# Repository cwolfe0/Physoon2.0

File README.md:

# Physoon2.0
This is the Eagle schematic and board file for the Physoon 2.0 (HAB Geiger Counters).
It externally interfaces with 2 geiger counters and processes the data before sending it via APRS and saving it on an SD card.

The board uses a:
- GPS
- Magnetometer
- MCU
- 5V Regulator
- 3.3V Regulator
- 6 Surefire CR123A in parallel sets of 3 in series.
- APRS-capable Radio
- 2 Logic Gates (for allowing 5V input to the radio from the MCU)
- Pressure Sensor
- Thermistor
- ON-MOM Switch
- PDI Interface

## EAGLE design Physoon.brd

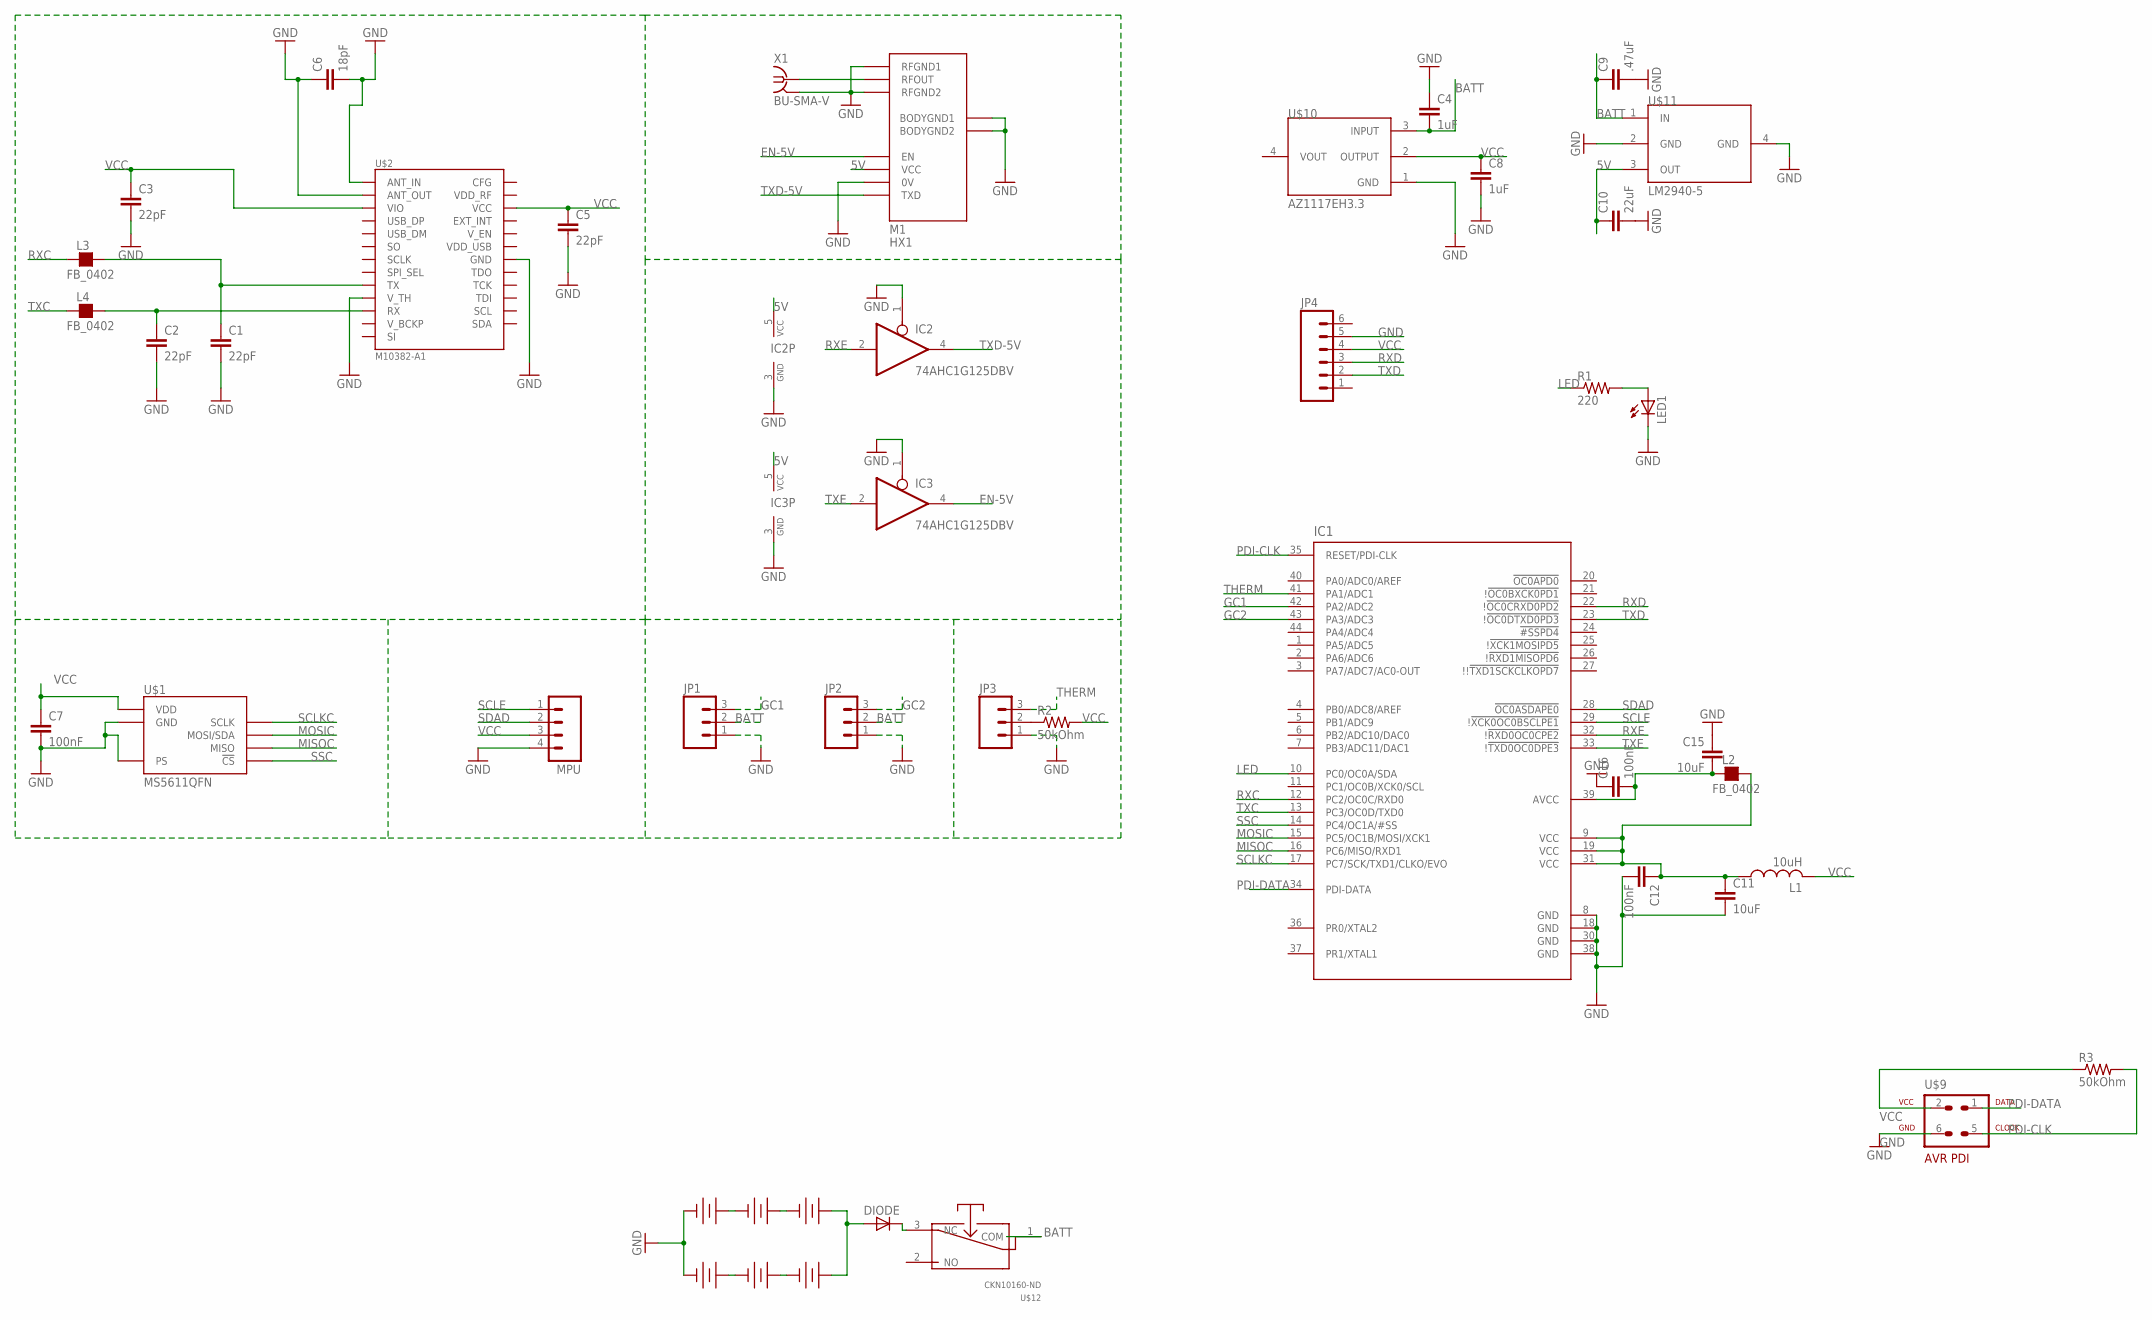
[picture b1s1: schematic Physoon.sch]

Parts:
C1, C2, C3, C5: 22pF; 0805
C4, C8: 1uF; 0603-CAP
C6: 18pF; 0805
C7, C12, C16: 100nF; 0805
C9: .47uF; 0603-CAP
C10: 22uF; 0603-CAP
C11, C15: 10uF; 0805
DIODE: LILYPAD-WEARABLES_LED1206; LILYPAD-WEARABLES_LED-1206
IC1: AT-XMEGA-XXA4-AU; QFP80P1200X1200X120-44N
IC2, IC3: 74AHC1G125DBV; SOT23-5
JP1, JP2, JP3: M03JST-PTH; JST-3-PTH
JP4: M06POLAR; MOLEX-1X6
L1: 10uH; L2012C
L2, L3, L4: FB_0402; L0402
LED1: LEDCHIP-LED0603; CHIP-LED0603
M1: HX1
MPU: M04; 04P
R1: 220; R0603
R2, R3: 50kOhm; 0805
U$1: MS5611QFN; MS5611-01BA01
U$2: M10382-A1
U$3, U$4, U$5, U$6, U$7, U$8: 123_BATTERY_HOLDERCR-123-A; CR-123-A_HOLDER
U$9: AVR-PDIVERT; AVR-ISP-6
U$10: AZ1117EH3.3; SOT-223
U$11: LM2940-5; SOT-223
U$12: CKN10160-ND; ZMCHFL3R
X1: BU-SMA-V

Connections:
5V: C10.1, IC2.5 (VCC), IC3.5 (VCC), M1.VCC, U$11.3 (OUT)
BATT: C4.2, C9.1, JP1.2, JP2.2, U$10.3 (INPUT), U$11.1 (IN), U$12.1 (COM)
EN-5V: IC3.4 (O), M1.EN
GC1: IC1.42 (PA2/ADC2), JP1.3
GC2: IC1.43 (PA3/ADC3), JP2.3
GND: C1.2, C2.2, C3.2, C4.1, C5.2, C6.1, C6.2, C7.2, C8.2, C9.2, C10.2, C11.2, C12.2, C15.1, C16.1, IC1.8 (GND), IC1.18 (GND), IC1.30 (GND), IC1.38 (GND), IC2.1 (OE), IC2.3 (GND), IC3.1 (OE), IC3.3 (GND), JP1.1, JP2.1, JP3.1, JP4.5, LED1.C, M1.0V, M1.BODYGND1, M1.BODYGND2, M1.RFGND1, M1.RFGND2, MPU.4, U$1.2 (PS), U$1.3 (GND), U$2.1 (ANT_IN), U$2.2 (GND), U$2.3 (ANT_OUT), U$2.4 (GND), U$2.12 (V_TH), U$2.14 (GND), U$2.17 (GND), U$2.21 (GND), U$2.24 (GND), U$2.26 (GND), U$2.28 (GND), U$2.33 (GND), U$2.34 (GND), U$2.35 (GND), U$2.36 (GND), U$3.-, U$6.-, U$9.6, U$10.1 (GND), U$11.2 (GND), U$11.4 (GND), X1.2 (GND), X1.3 (GND), X1.4 (GND), X1.5 (GND)
LED: IC1.10 (PC0/OC0A/SDA), R1.1
MISOC: IC1.16 (PC6/MISO/RXD1), U$1.6 (MISO)
MOSIC: IC1.15 (PC5/OC1B/MOSI/XCK1), U$1.7 (MOSI/SDA)
unnamed: C1.1, L3.2, U$2.11 (TX)
unnamed: C2.1, L4.2, U$2.13 (RX)
unnamed: U$3.+, U$4.-
unnamed: M1.RFOUT, X1.1
unnamed: U$4.+, U$5.-
unnamed: DIODE.A, U$5.+, U$8.+
unnamed: U$6.+, U$7.-
unnamed: U$7.+, U$8.-
unnamed: LED1.A, R1.2
unnamed: DIODE.C, U$12.3 (NC)
unnamed: JP3.2, R2.1
unnamed: C15.2, C16.2, IC1.39 (AVCC), L2.1
unnamed: C11.1, C12.1, IC1.9 (VCC), IC1.19 (VCC), IC1.31 (VCC), L1.1, L2.2
PDI-CLK: IC1.35 (RESET/PDI-CLK), R3.2, U$9.5
PDI-DATA: IC1.34 (PDI-DATA), U$9.1
RXC: IC1.12 (PC2/OC0C/RXD0), L3.1
RXD: IC1.22 (!!OC0CRXD0PD2), JP4.3
RXE: IC1.32 (!!RXD0OC0CPE2), IC2.2 (I)
SCLE: IC1.29 (!!XCK0OC0BSCLPE1), MPU.1
SCLKC: IC1.17 (PC7/SCK/TXD1/CLKO/EVO), U$1.8 (SCLK)
SDAD: IC1.28 (!OC0ASDAPE0), MPU.2
SSC: IC1.14 (PC4/OC1A/#SS), U$1.4 (!CS!), U$1.5 (!CS!)
THERM: IC1.41 (PA1/ADC1), JP3.3
TXC: IC1.13 (PC3/OC0D/TXD0), L4.1
TXD: IC1.23 (!!OC0DTXD0PD3), JP4.2
TXD-5V: IC2.4 (O), M1.TXD
TXE: IC1.33 (!!TXD0OC0DPE3), IC3.2 (I)
VCC: C3.1, C5.1, C7.1, C8.1, JP4.4, L1.2, MPU.3, R2.2, R3.1, U$1.1 (VDD), U$2.5 (VIO), U$2.27 (VCC), U$9.2, U$10.2 (OUTPUT)

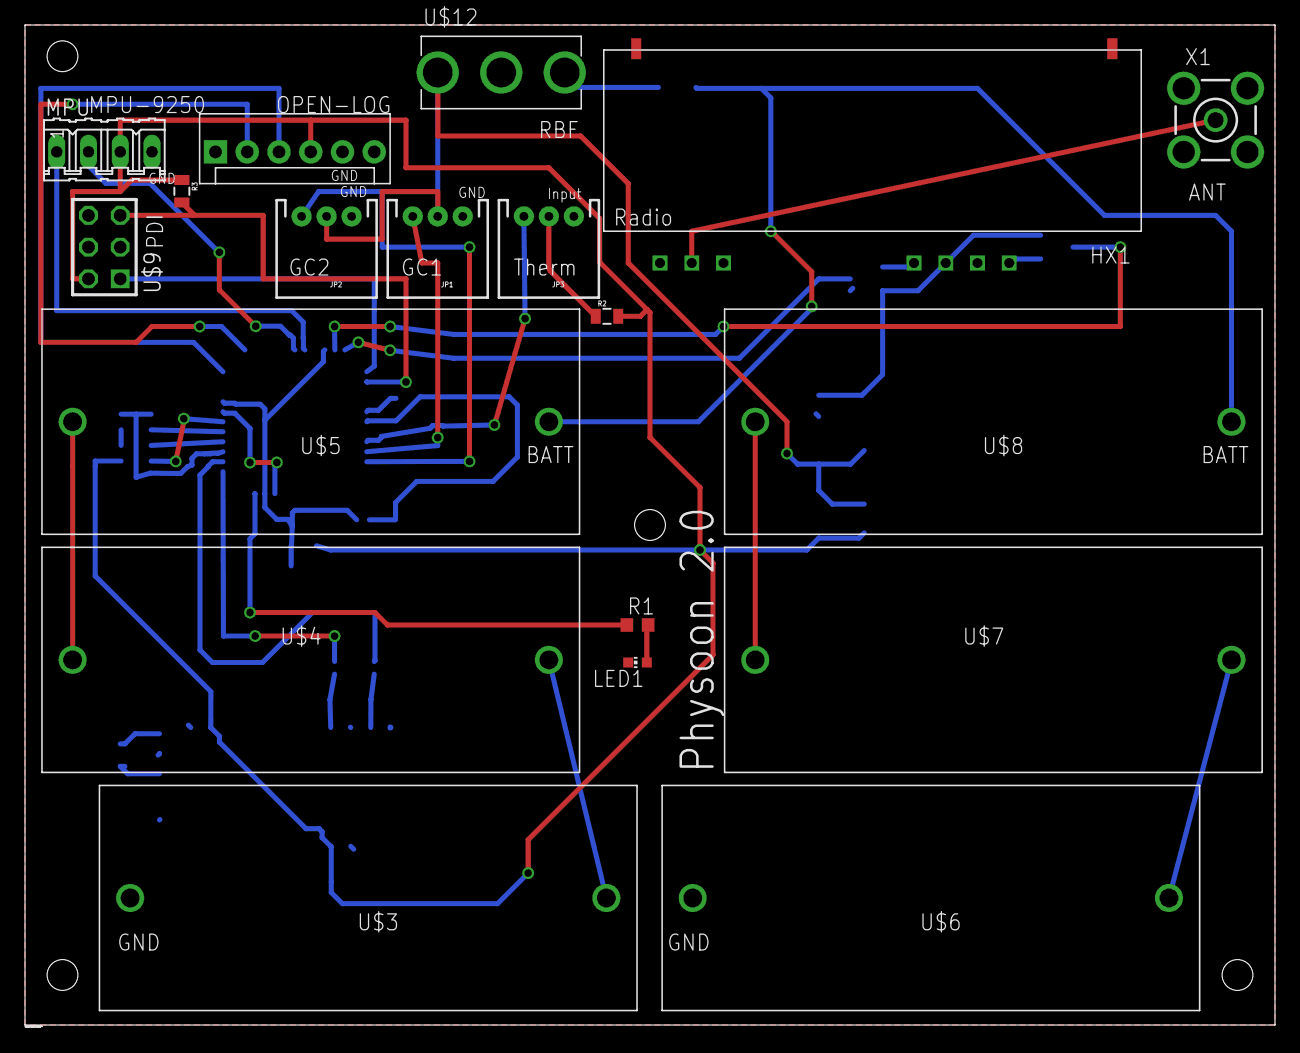
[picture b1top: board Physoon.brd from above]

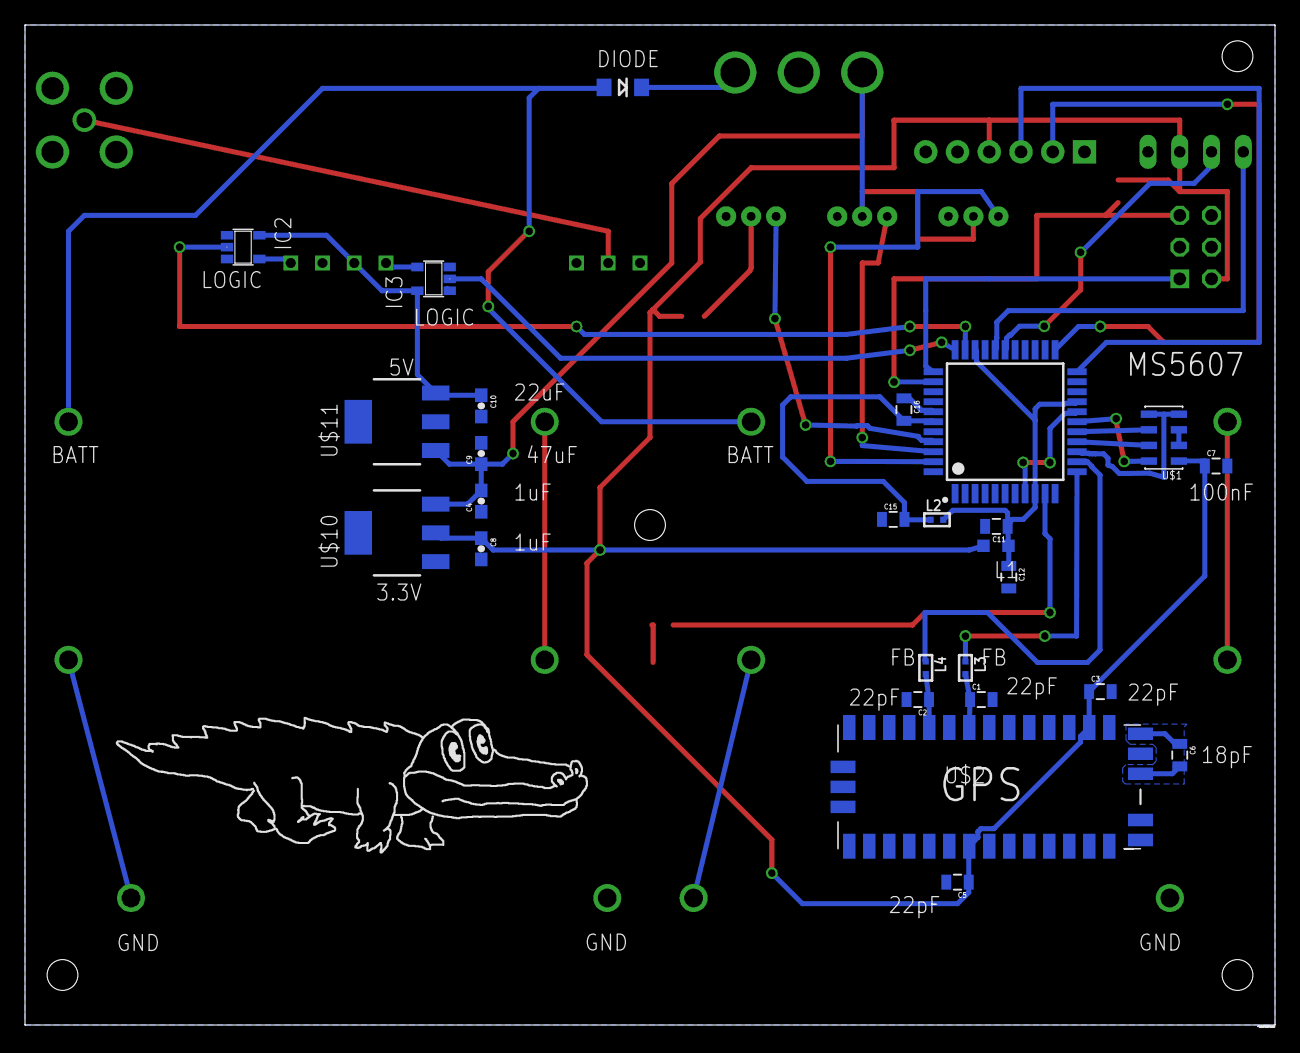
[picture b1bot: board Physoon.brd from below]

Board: 2 copper layers, 100.0 x 80.2 mm, 45 parts (26 on the bottom side), 37 nets.

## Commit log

2017-04-08 Schematics
2017-04-09 April 8th work.
2017-04-09 New Volt Reg Lib
2017-04-10 Both Voltage Regs added and made
2017-04-10 Fixes for names
2017-04-10 More work
2017-04-10 Starting Board Work (caps near component they're for)
2017-04-10 Rev1. of Board Done
2017-04-10 Added Silkscreen
2017-04-10 Confirmation of distances
2017-04-10 First Revision for Checking
2017-04-10 Add readme info
2017-04-10 Board Image
2017-04-10 add board image
2017-04-10 Show Ground Planes
2017-04-11 4/10 Updates
2017-04-13 Flipped and moved Croc, add gerbers
2017-04-13 Fix GND being way off board
2017-04-13 New pictures on Readme
2017-04-13 Move Gerbers to Main.zip
2017-04-13 Remove ground graces
2017-04-17 Add LED for nerde programmers
2017-04-19 Consolidating boards, fixing library folder
2017-04-19 Gerbers Made and zipped
2017-04-21 Move LED to "the right" port
2017-04-21 Make croc larger, fix board files
2017-04-24 add diode
2017-04-24 remove uneccesary files
2017-05-14 fix interface for IMU
2017-05-14 fix airwires and add fixed resistor for thermistor
2017-05-14 removing random # files
2017-05-25 Cleaning up for Production
2017-05-25 Add MCU power filtering, fix drill sizes to Sparkfun DRU
2017-05-25 Fix PDI
2017-05-25 remove old zip
2017-06-21 Fix resistor value on PDI lane
2017-06-21 remove *#* files
2017-07-18 Fix GPS wiring
2017-08-12 fixing some things

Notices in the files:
parts and their libraries:
SparkFun: Licensing: CC v3.0 Share-Alike You are welcome to use this library for commercial purposes.
rc-master-smd: Copyright (C) 2007, Bob Starr
